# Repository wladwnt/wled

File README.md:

# WLED

**Jetzt gibt es mehrere kommerzielle professionelle Versionen dieses Boards:**
* **NEW:** [ESP32 basiert, für 5V/12V/24V LEDs](https://shop.myhome-control.de/ABC-WLED-Controller-Board-5-24V/HW10015), zu kaufen [in meinem Shop](https://shop.myhome-control.de/ABC-WLED-Controller-Board-5-24V/HW10015); Auch [Ethernet Adapter verfügbar in meinem Shop](https://shop.myhome-control.de/Ethernet-Adapter-fuer-WLED-Controller/HW10016)
* [ESP32 basiert](https://shop.myhome-control.de/ABC-WLED-Controller-V41-ESP32/HW10003.1), zu kaufen [in meinem Shop](https://shop.myhome-control.de/ABC-WLED-Controller-V41-ESP32/HW10003.1)
* [Universelles WLED Shield für 5V / 12V LED Strips](https://shop.myhome-control.de/ABC-WLED-Basis-Board-fuer-5V-und-12V-LED-universell/HW10008), zu kaufen auch [in meinem Shop](https://shop.myhome-control.de/ABC-WLED-Basis-Board-fuer-5V-und-12V-LED-universell/HW10008)
* [Mini Controller Board mit ESP32](https://shop.myhome-control.de/ABC-WLED-Controller-Board-mini-5V-12V-ESP32/HW10014), zu kaufen auch [in meinem Shop](https://shop.myhome-control.de/ABC-WLED-Controller-Board-mini-5V-12V-ESP32/HW10014)
* Auch ein passendes Relais Board in meinem shop, versionen: [5V](https://shop.myhome-control.de/Relais-Board-fuer-WLED-Controller/HW10005), [12V](https://shop.myhome-control.de/Relais-Board-fuer-WLED-Controller-12V/HW10011) oder [24V](https://shop.myhome-control.de/Relais-Board-fuer-WLED-Controller-24V/HW10017)
* Und auch ein Line-In zu I2S Adapter für Sound Reactive WLED [in meinem Shop](https://shop.myhome-control.de/Line-In-zu-I2S-Adapter-fuer-WLED-Controller/HW10013)

Fragen? Kontaktieren Sie mich via Email: wled.controller@gmx.de

Einfaches WLED Board
 - Für 5V and 12V LED Streifen (unterschiedliche Bestückung möglich)
 - Beispiele für die Verbindung mit dem Netzteil/LED
 - Einfache Montage, Kein Kabelsalat, technisch saubere und sichere Ausführung
 - Software: https://github.com/Aircoookie/WLED
 - ESP32 in D1 mini Format kann anstatt ESP8266 verwendet werden, passt auch drauf (in WLED Konfiguration muss man dann GPIO 16 für Data und ggf. GPIO 17 für Clock einstellen).

## Die Platine (hier bestückt als Version für 5V LED)

## Bestückt als Version für 12V LED mit WS2815 LED Streifen:

## Examples for connection

## How it works

Alle Rechte sind vorbehalten. Jegliche kommerzielle Nutzung der Inhalte ohne Zustimmung des Autors ist nicht gestattet.

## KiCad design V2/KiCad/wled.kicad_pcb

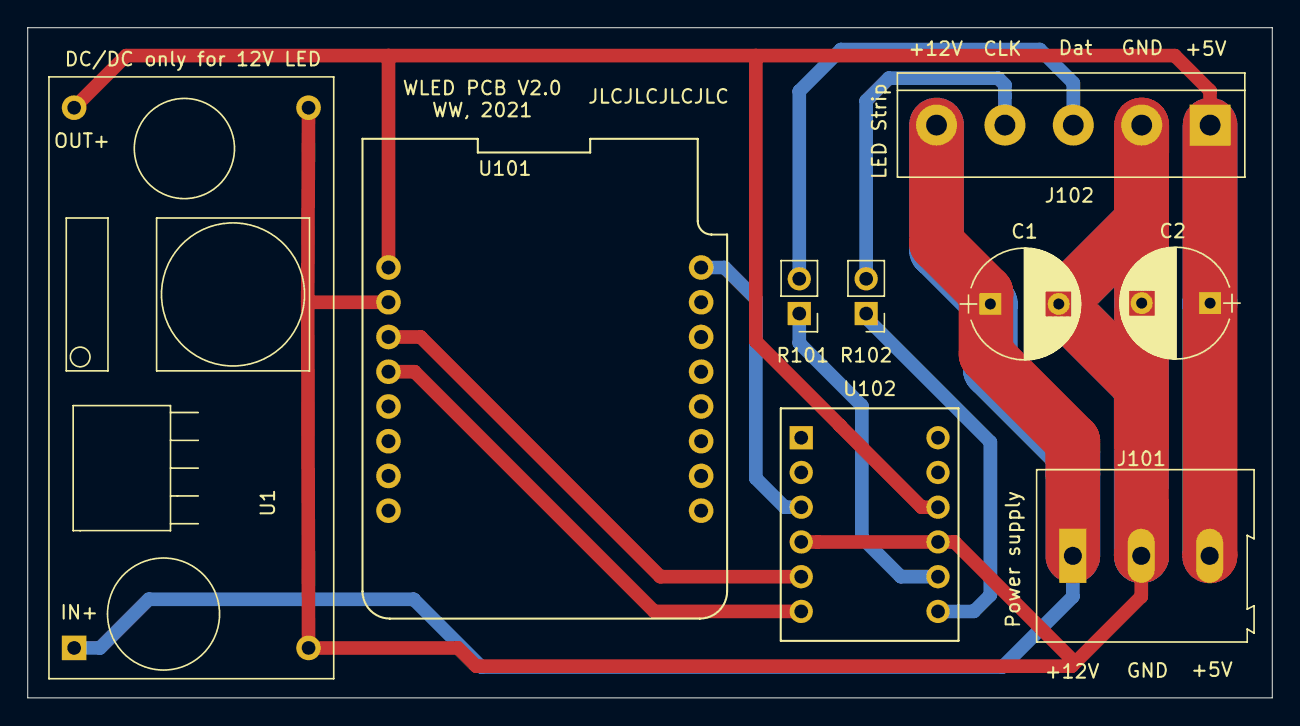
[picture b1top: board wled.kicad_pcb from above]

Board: 2 copper layers, 91.0 x 49.0 mm, 9 parts (0 on the bottom side), 10 nets.

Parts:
C1, C2: CP; CP_Radial_D8.0mm_P5.00mm
J101: Conn_01x02_Female; TerminalBlock_Altech_AK300-3_P5.00mm
J102: Conn_01x04_Female; TerminalBlock_5_P5.0mm
R101, R102: 470; Pin_Header_Straight_1x02_Pitch2.54mm
U1: LM2596_Module
U101: WeMos_D1_mini; wemos-d1-mini-connectors-only
U102: LevelShifter

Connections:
/+5V: C2.1, J101.3, J102.1, U1.3, U101.9, U102.9
/+12V: C1.1, J101.1, J102.5, U1.1
/GND: C1.2, C2.2, J101.2, J102.2, U1.2, U1.4, U101.10, U102.4, U102.10
unnamed: J102.3, R101.2
unnamed: J102.4, R102.2
unnamed: R101.1, U102.11
unnamed: R102.1, U102.12
unnamed: U101.8, U102.3
unnamed: U101.11, U102.5
unnamed: U101.12, U102.6
